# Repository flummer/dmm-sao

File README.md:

# SAO Digital Multimeter

Additional documentation and build log can be found on the [hackaday.io project page for the SAO Digital Multimeter](https://hackaday.io/project/198892-sao-digital-multimeter)

## Features

- Resistance measurement and LED test (including continuity test with a buzzer)
- SAO Input voltage measurement
- SAO GPIO voltage measurement
- I2C info (WIP)

## Firmware

This is designed to run CircuitPython and there is [a custom build](https://github.com/flummer/circuitpython/tree/hxr-sao-dmm) with the needed libraries included, and meaningful pin names for easier development.

A binary build of this is included under `firmware/firmware.uf2` and the application code (`code.py`) and resource files are also in the `firmware` folder.

### Initial programming or CircuitPython updating

- Connect the SAO DMM to a computer usig a USB-C cable and hold down the `Boot` button, when pressing the `Reset` button.
- A new drive should show up called `RPI-RP2`, and you simply copy the `firmware.uf2` file to this drive.
- When the copy is done, the device will disconnect and reboot.
- A new drive will show up named `CIRCUITPY`, and here you need to copy the remaining files in the `firmware` folder to the root folder of the `CIRCUITPY` device.
- The device will not disconnect, but will do one or more reboots, and after that, you are done.

During this, you might be asked or be blocked by your operating system, as sometimes you will need to verify access to new, unknown devices.

## Case and other 3D printed parts

The case and all the button caps, the main knob, and internal spacers to make sure everything sits correctly are designed to be 3D printed with a regular consumer printer. They have been tweaked to be printable with a 0.4mm nozzle, but using a smaller one (eg. 0.2mm) will allow you to use thinner layers, at least in some places, to get a smoother top finnish (top of main knob and top of button caps really benefit from that).

There are also files for a set of 3D printable probes, that are designed to be assembled without any tools, sandwitched around a thin probe wire soldered to a P100-B1 pogo pin for the tip.

There is a `.3mf` file in the `case` folder with a project for BambuLab printers, including 5 plates, one for each color needed.

## Designed in KiCad v8.99 (nightly)

To open the project, you will need to install a recent nightly build (og v9 or newer when released), KiCad v8 or earlier won't open this design directly.

[Electronics schematics as a PDF file](https://github.com/flummer/dmm-sao/blob/main/DMM%20SAO%20Schematics.pdf) is also included for reference.

## License

The hardware design (both electronics and 3D designs) of the `main` branch of this repository is released under the following license:

* the "Creative Commons Attribution-ShareAlike 4.0 International License"
  (CC BY-SA 4.0) full text of this license is included in the LICENSE file
  and a copy can also be found at
  [http://creativecommons.org/licenses/by-sa/4.0/](http://creativecommons.org/licenses/by-sa/4.0/)

The CircuitPython firmware (including the python application code) is released under the MIT license with smaller dependencies under other licenses as detailed in [its LICENSE](https://github.com/flummer/circuitpython/blob/hxr-sao-dmm/LICENSE) and [LICENSE_MicroPython](https://github.com/flummer/circuitpython/blob/hxr-sao-dmm/LICENSE_MicroPython) files.

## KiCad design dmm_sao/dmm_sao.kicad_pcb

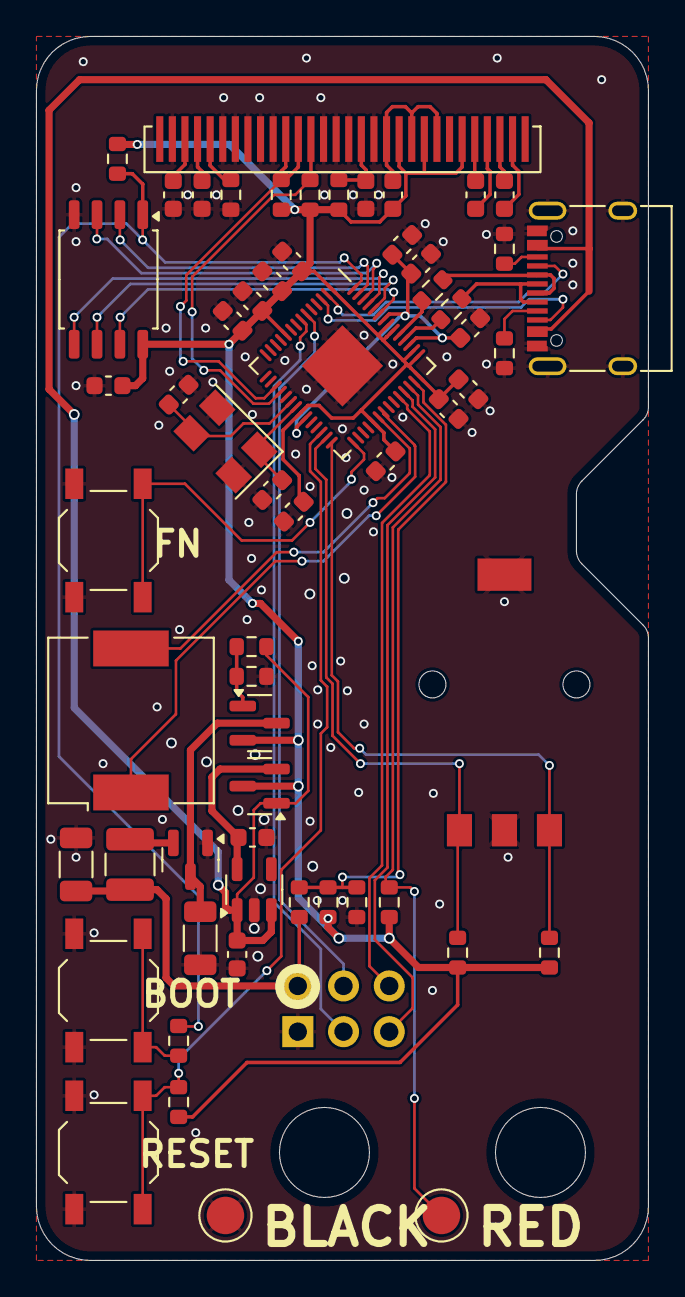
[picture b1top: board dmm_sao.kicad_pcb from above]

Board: 2 copper layers, 34.0 x 68.0 mm, 63 parts (0 on the bottom side), 49 nets.

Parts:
C1, C2, C3, C7, C9: 1uF; C_0603_1608Metric
C4, C11, C18, C23: 2.2uF; C_0603_1608Metric
C5, C12, C13, C14, C15, C16, C17, C19, C20, C24: 100nF; C_0603_1608Metric
C6: 10uF; C_0603_1608Metric
C8, C10: 100uF; C_1206_3216Metric
C21, C22: 30pF; C_0603_1608Metric
FRONT: Case
J1: RED_MEASURE; TestPoint_Pad_D2.5mm
J2: BLK_GND; TestPoint_Pad_D2.5mm
J3: USB_C; USB_C_Receptacle_XKB_U262-16XN-4BVC11
L1: 47uH; L_1210_3225Metric
LS1: OWPB-909018S-40-03; Buzzer_CUI_CPT-9019S-SMT
OLEDM1: SSD1306; IROP055-SSD1306Z-PADS-ONLY
Q1: CJ2302; SOT-23
Q2: CJ2305; SOT-23
R1: 100R; R_0603_1608Metric
R2, R5, R6, R7, R18, R19: 10K; R_0603_1608Metric
R3: 3K3; R_0603_1608Metric
R4: 4K7; R_0603_1608Metric
R8: 330K; R_0603_1608Metric
R9: 4.7k; R_0603_1608Metric
R10: 6.8k; R_0603_1608Metric
R11, R12: 5.1k; R_0603_1608Metric
R13: 1k; R_0603_1608Metric
R14, R15: 27R; R_0603_1608Metric
R16, R17: 10k; R_0603_1608Metric
SCREEN_SUPPORT: Case
SW1, SW3, SW4: TS5220A; SW_SPST_TL3342
SW2: RotaryEncoder; EVQ-VV
U1: HX9193-33GB; SOT-23-5
U2: QX2304; SOT-23
U3: W25QXX128MBIT; SOIC-8_5.23x5.23mm_P1.27mm
U4: RP2040; QFN-56_EP_7x7_Pitch0.4mm
X1: Badgelife_sao_connector_v169bis; Badgelife-SAOv169-SAO-2x3
Y1: 12MHz, 20pF; Crystal_SMD_5032-4Pin_5.0x3.2mm

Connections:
+1V1: C18.1, C19.1, C20.1, U4.23 (DVDD), U4.45 (VREG_VOUT), U4.50 (DVDD)
/DMM Measure/MEASURE_RES: J1.1, R1.2, U4.40 (GPIO28)
/DMM Measure/MEASURE_VIN: R2.2, R3.1, R4.1, U4.41 (GPIO29)
/PSU/BOOST_OUT: C10.1, Q2.3 (D), U2.3 (VOUT)
/PSU/VREG_OUT: C9.1, Q1.2 (S), U1.5 (VOUT)
/RP2040/D+: R15.2, U4.47 (USB_D+)
/RP2040/D-: R14.2, U4.46 (USB_D-)
/RP2040/QSPI-0: U3.5 (DI(IO0)), U4.53 (QSPI_SD0)
/RP2040/QSPI-1: U3.2 (DO(IO1)), U4.55 (QSPI_SD1)
/RP2040/QSPI-2: U3.3 (IO2), U4.54 (QSPI_SD2)
/RP2040/QSPI-3: U3.7 (IO3), U4.51 (QSPI_SD3)
/RP2040/QSPI-CLK: U3.6 (CLK), U4.52 (QSPI_SCLK)
/RP2040/QSPI-~CS: R13.2, R17.2, U3.1 (~CS), U4.56 (~QSPI_CS)
/RP2040/SBU1: J3.A8 (SBU1), U4.2 (GPIO0)
/RP2040/SBU2: J3.B8 (SBU2), U4.3 (GPIO1)
/RP2040/SPI_COPI/G7: LS1.1, U4.35 (GPIO23)
/RP2040/SPI_SCK/G6: LS1.2, U4.34 (GPIO22)
/RP2040/USB_D+: J3.A6 (D+), J3.B6 (D+), R15.1
/RP2040/USB_D-: J3.A7 (D-), J3.B7 (D-), R14.1
/RP2040/~BOOT: R13.1, SW4.2 (B)
/RP2040/~RESET: R16.2, SW3.2 (B), U4.26 (RUN)
BTN_FN: SW1.2 (B), U4.29 (GPIO18)
ENC_A: R18.1, SW2.A, U4.27 (GPIO16)
ENC_B: R19.1, SW2.B, U4.28 (GPIO17)
GND: C4.2, C5.1, C6.2, C7.2, C8.2, C9.2, C10.2, C11.2, C12.2, C13.2, C14.2, C15.2, C16.2, C17.2, C18.2, C19.2, C20.2, C21.1, C22.1, C23.2, C24.2, J2.1, J3.A1 (GND), J3.A12 (GND), J3.B1 (GND), J3.B12 (GND), J3.S1 (SHIELD), OLEDM1.13 (CS#), OLEDM1.15 (C/D#), OLEDM1.16 (R/W#), OLEDM1.17 (E_RD#), OLEDM1.21 (DB3), OLEDM1.22 (DB4), OLEDM1.23 (DB5), OLEDM1.24 (DB6), OLEDM1.25 (DB7), OLEDM1.29 (VLSS), R4.2, R8.2, R10.2, R11.1, R12.1, SW1.1 (A), SW2.C, SW3.1 (A), SW4.1 (A), U1.2 (GND), U2.1 (GND), U3.4 (GND), U4.19 (TESTEN), U4.57 (GND), X1.2 (GND), Y1.2, Y1.4
I2C0_SCL: U4.7 (GPIO5), X1.4 (SCL)
I2C0_SDA: U4.6 (GPIO4), X1.3 (SDA)
I2C1_SCL: OLEDM1.18 (DB0), R7.2, U4.18 (GPIO15)
I2C1_SDA: OLEDM1.19 (DB1), OLEDM1.20 (DB2), R6.2, U4.17 (GPIO14)
unnamed: J3.A5 (CC1), R11.2
unnamed: J3.B5 (CC2), R12.2
unnamed: C3.2, OLEDM1.8 (VSS), OLEDM1.10 (BS0), OLEDM1.12 (BS2)
unnamed: C2.2, OLEDM1.5 (CAP1N)
unnamed: C2.1, OLEDM1.4 (CAP1P)
unnamed: C1.2, OLEDM1.3 (CAP2N)
unnamed: C1.1, OLEDM1.2 (CAP2P)
unnamed: OLEDM1.26 (IREF), R8.1
unnamed: C5.2, OLEDM1.14 (RES#), R5.2
unnamed: C4.1, OLEDM1.28 (VCC)
unnamed: C6.1, OLEDM1.27 (VCOMH)
unnamed: Q2.1 (G), R9.2, R10.1
unnamed: L1.2, U2.2 (LX)
unnamed: C21.2, U4.20 (XIN), Y1.3
unnamed: C22.2, U4.21 (XOUT), Y1.1
SAO_GPIO1: U4.38 (GPIO26), X1.5 (GPIO1)
SAO_GPIO2: U4.39 (GPIO27), X1.6 (GPIO2)
SAO_VIN: C8.1, L1.1, R2.1, X1.1 (VCC)
USB_BUS_POWER: C7.1, J3.A4 (VBUS), J3.A9 (VBUS), J3.B4 (VBUS), J3.B9 (VBUS), Q1.1 (G), R9.1, U1.1 (VIN), U1.3 (EN)
VCC: C3.1, C11.1, C12.1, C13.1, C14.1, C15.1, C16.1, C17.1, C23.1, C24.1, OLEDM1.6 (VBAT), OLEDM1.9 (VDD), OLEDM1.11 (BS1), Q1.3 (D), Q2.2 (S), R1.1, R3.2, R5.1, R6.1, R7.1, R16.1, R17.1, R18.2, R19.2, U3.8 (VCC), U4.1 (IOVDD), U4.10 (IOVDD), U4.22 (IOVDD), U4.33 (IOVDD), U4.42 (IOVDD), U4.43 (ADC_AVDD), U4.44 (VREG_VIN), U4.48 (USB_VDD), U4.49 (IOVDD)

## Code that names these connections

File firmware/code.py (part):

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
# Pin usage:
# -------------------------
# Screen SCL: GPIO15 / DISPLAY_SCL
# Screen SDA: GPIO14 / DISPLAY_SDA
# Buzzer A: GPIO22 / BUZZER_A
# Buzzer B: GPIO23 / BUZZER_B
# Vin Measure: A3 / GPIO29 / MEASURE_VIN
# Res Measure: A2  / GPIO28 / MEASURE_RES
# ENC_A: GPIO16 / ENC_A
# ENC_B: GPIO17 / ENC_B
# Fn: GPIO18 / BUTTON_FN
# SAO SCL: GPIO5 / SAO_SCL
# SAO SDA: GPIO4 / SAO_SDA
# SAO GPIO1: A0 / GPIO26 / SAO_GPIO1
# SAO GPIO2: A1 / GPIO27 / SAO_GPIO2

## Release display, as Circuitpython will be using it during reboot when saving
displayio.release_displays()
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smallfont = bitmap_font.load_font("firecracker16.bdf")

# Setup different pins
gpio1_in = AnalogIn(board.SAO_GPIO1)
gpio2_in = AnalogIn(board.SAO_GPIO2)

res_in = AnalogIn(board.MEASURE_RES)
sao_vin = AnalogIn(board.MEASURE_VIN)
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io_caption = label.Label(smallfont, text=text, color=0xFFFF00, x=0, y=10)
io_panel.append(io_caption)

text = "GPIO1"
io1_caption = label.Label(smallfont, text=text, color=0xFFFF00, x=0, y=30)
io_panel.append(io1_caption)

text = "GPIO2"
io2_caption = label.Label(smallfont, text=text, color=0xFFFF00, x=0, y=50)
io_panel.append(io2_caption)

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    elif (enc_a.value & (not enc_b.value)) and main_mode != 2: # Vin reading mode
        main_mode = 2
        display.root_group = vin_panel
    elif ((not enc_a.value) & (not enc_b.value)) and main_mode != 3: # GPIO mode
        main_mode = 3
        display.root_group = io_panel
    elif ((not enc_a.value) & enc_b.value) and main_mode != 4: # I2C mode (WIP)
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
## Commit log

2024-10-22 Added 3D printed parts
2024-10-22 Added license, readme and some images
2024-11-19 Moved buzzer to base board
    Also:
    - Moved a few parts to make space for the buzzer
    - Connected the buzzer in a push/pull setup for better volume
    - Changed the edgecut a little, to have better space for knob intent mechanism in case
    - Tweaked pads for spring loaded pins to match manufacturer suggestion
    - Made the paste for the display connector 10% smaller
2024-11-19 Added 1x5 panel of the base board
2024-11-19 Updated 3D print files to match v1.1
2024-11-19 Added 3D printable mini probe handle
2024-11-19 Updated ibom to match v1.1
2024-12-02 Updated case to use 3D printed knob intent
    Eliminate need for steel ball
    Also added a little extra space for v-score left overs, when using panelized base PCB
2024-12-08 Updated 3D printed parts to better work with 0.4mm nozzle
    Also changed button caps to support tactile switches that are 2.0 mm high in addition to those that are 1.5 mm.
2024-12-08 Added printer project with slicer settings for 0.4mm nozzle on Bambu Lab printers
2024-12-08 Added firmware and updated readme
2024-12-08 Fixed typo
2025-01-19 Added logos and adjusted panel tooling holes
    Tool holes changed to be 1.152mm diameter, following JLCPCB assembly spec
    versions bumped to 1.2
2025-02-02 Added alternative design for the probe middle sleeve
    This is an attempts to improve the print performance on some printers, mainly limiting need for retraction during infill printing
2025-05-15 Updated code to match release at Hackaday Berlin 2025
2025-05-15 Updated CircuitPython firmware image to 9.2.7

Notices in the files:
firmware/code.py:
SPDX-FileCopyrightText: Copyright (c) 2024 Thomas Flummer for HXR.DK
SPDX-License-Identifier: MIT
